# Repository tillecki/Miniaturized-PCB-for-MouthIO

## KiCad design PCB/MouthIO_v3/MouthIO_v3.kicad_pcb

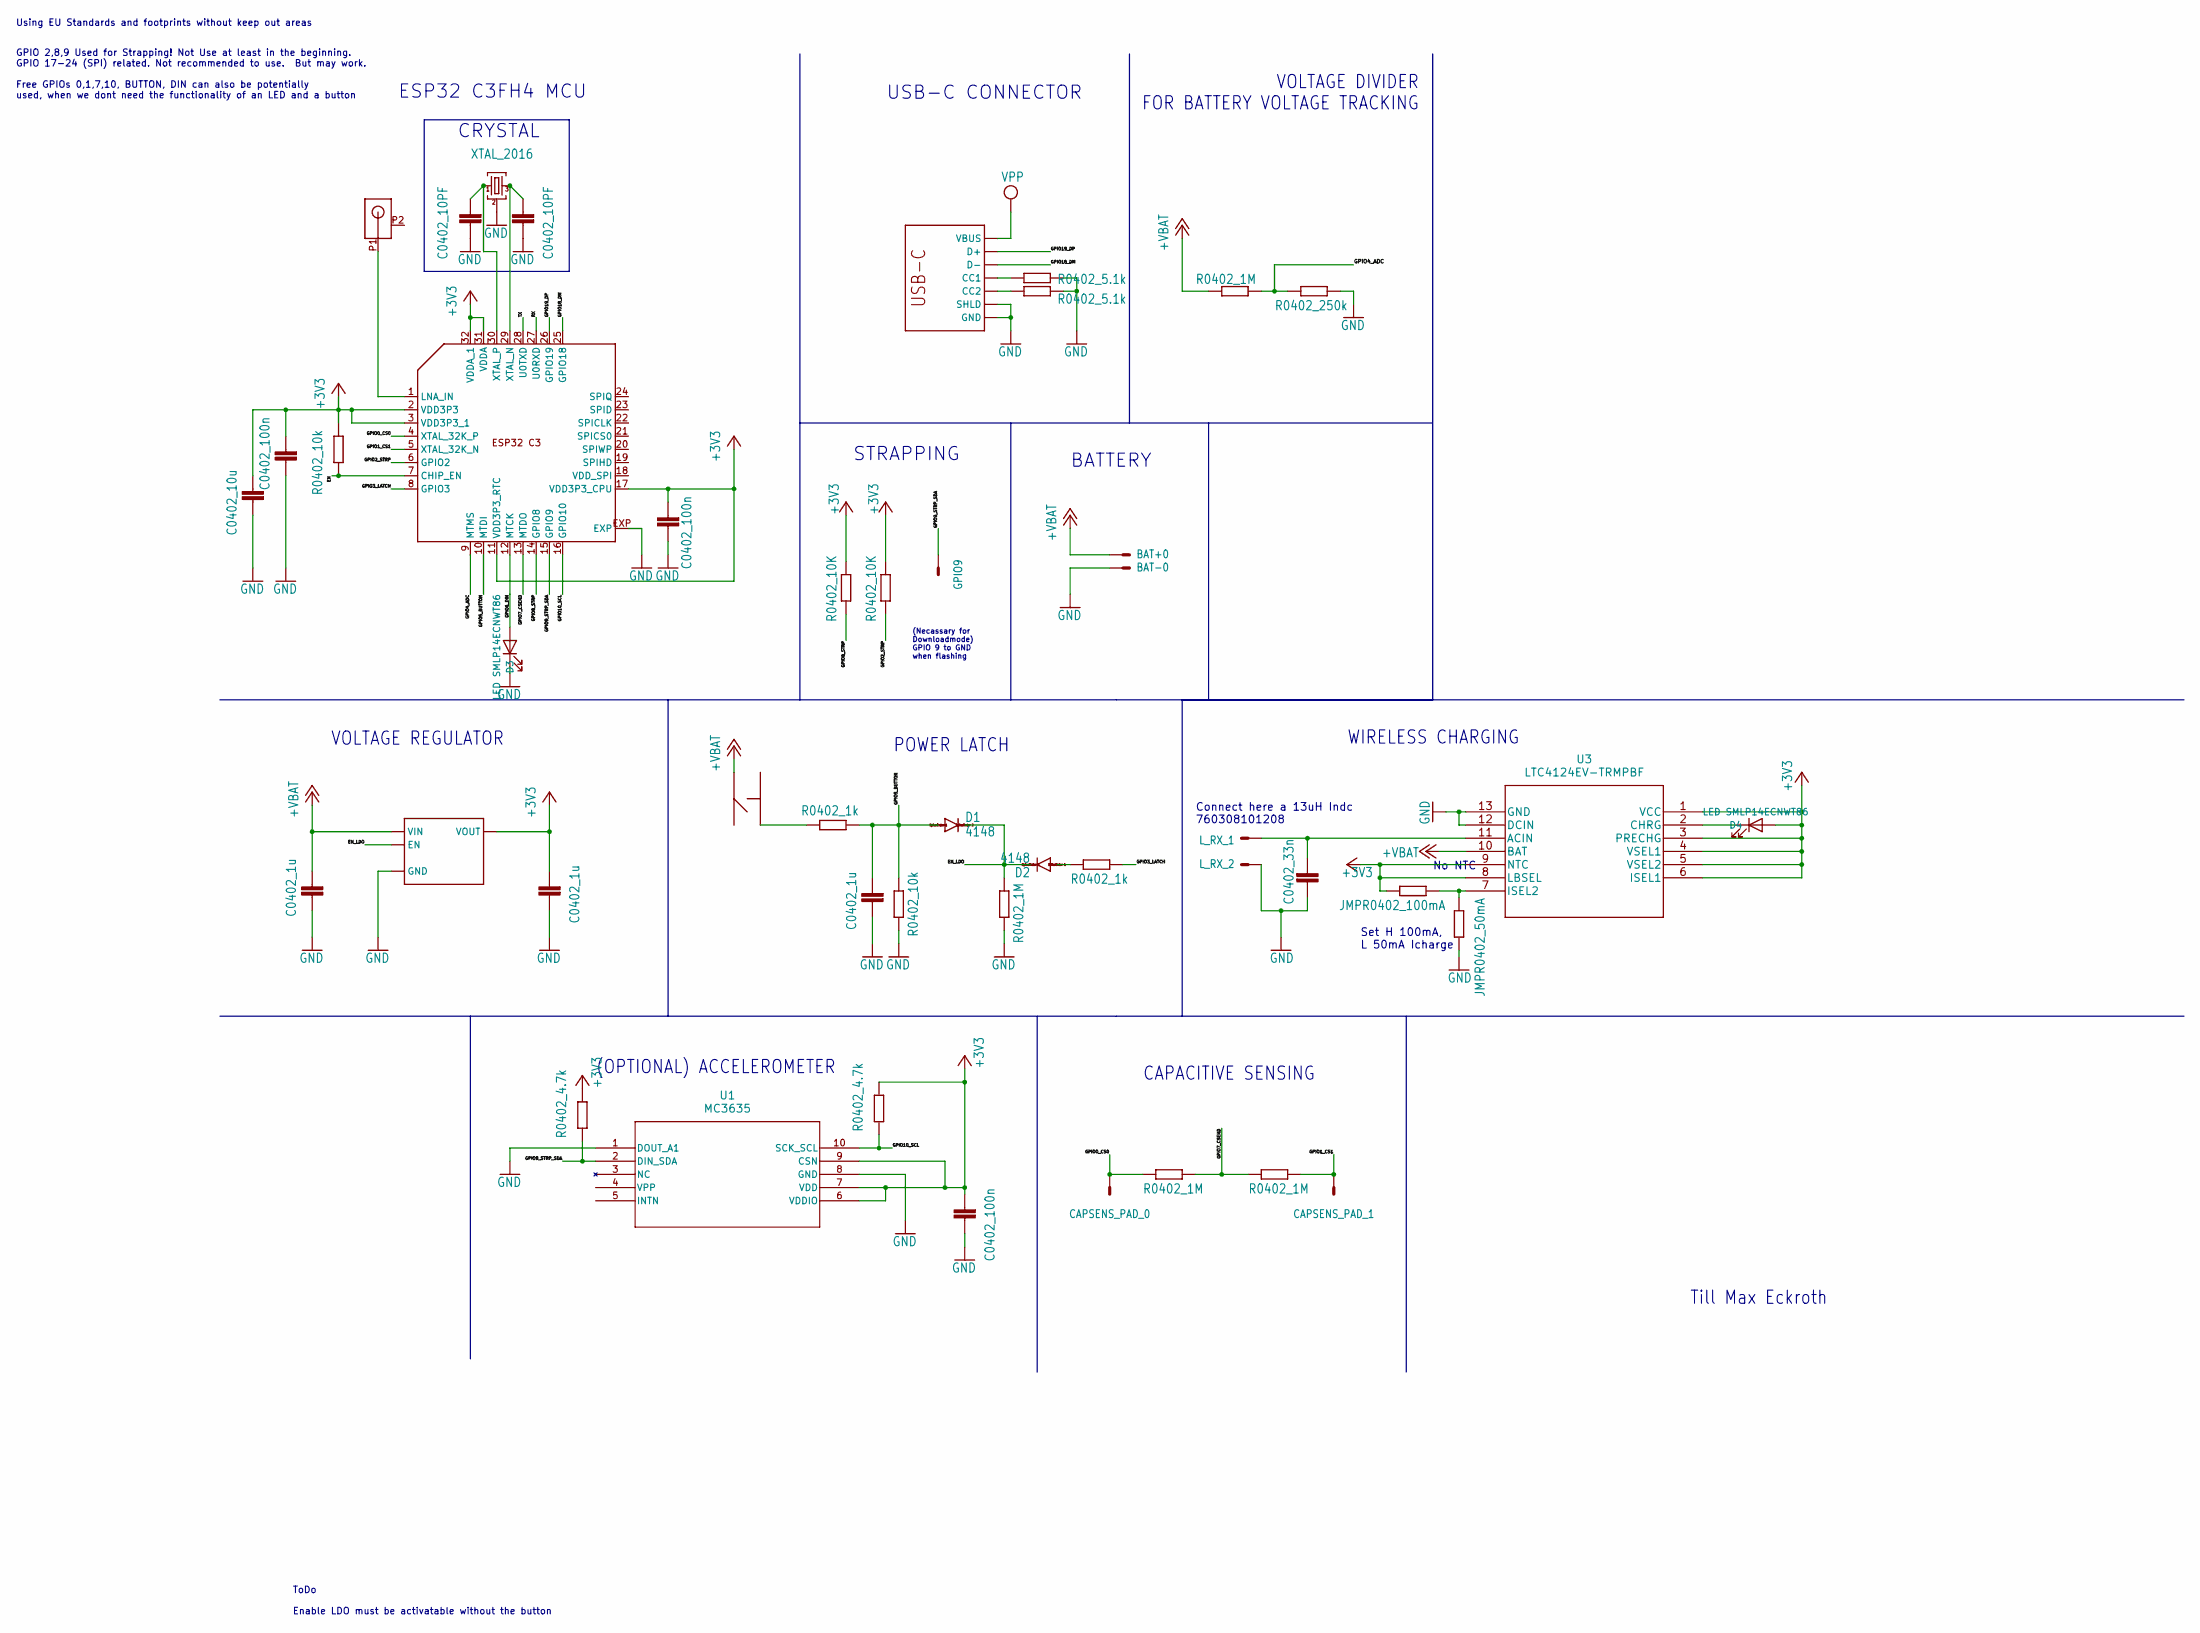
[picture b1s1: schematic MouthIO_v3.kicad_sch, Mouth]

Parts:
BAT+0: TP/SP-1.5X1.0; Solderpad_1.5_1.0
BAT-0: TP/SP-1.5X1.0; Solderpad_1.5_1.0
C1, C2, C13: C0402_1u; C0402_S
C3: C0402_100n; C_0402_1005Metric
C4: C0402_33n; C_0402_1005Metric
C7: C0402_10u; C0402_S
C8, C9: C0402_100n; C0402_S
C20, C21: C0402_10PF; C0402_S
CAPSENS_PAD_0, CAPSENS_PAD_1: TP/SP-1.5X1.0; Solderpad_1.5_1.0
D1, D2: 4148; SOD523
D3, D4: LED SMLP14ECNWT86; R_0402_1005Metric
ESP1: ESP32_C3_QFN32; QFN32
GPIO9: TP/SP-1.5X1.0; Solderpad_1.5_1.0
L_RX_1, L_RX_2: TP/SP-1.5X1.0; Solderpad_1.5_1.0
R1, R2: R0402_1k; R0402
R3: R0402_1M; R0402
R4, R7: R0402_10k; R0402
R5, R6: R0402_4.7k; R_0402_1005Metric
R8, R9: R0402_1M; R_0402_1005Metric
R10, R11: R0402_10K; R0402
R12, R13: R0402_5.1k; R0402
R15: JMPR0402_100mA; R_0402_1005Metric
R16: JMPR0402_50mA; R_0402_1005Metric
R/1: R0402_1M; R0402
R/2: R0402_250k; R0402
RF0: ANT3216LL00R2400A
U1: MC3635; MC3635_MEM-L
U2: MIC5504; TDFN4
U3: LTC4124EV-TRMPBF
U$1: BUTTON_ST-1187-3
USB-C0: USB_C_C393939; USBC_C393939
X1: XTAL_2016; XTYL_2016

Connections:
+3V3: C2.P$2 (2), C3.2, C7.P$2 (2), C8.P$2 (2), C9.P$2 (2), D4.2 (A), ESP1.2 (VDD3P3), ESP1.3 (VDD3P3_1), ESP1.11 (VDD3P3_RTC), ESP1.17 (VDD3P3_CPU), ESP1.31 (VDDA), ESP1.32 (VDDA_1), R5.1, R6.1, R7.1, R10.1, R11.1, R15.2, U1.6 (VDDIO), U1.7 (VDD), U1.9 (CSN), U2.P1 (VOUT), U3.1 (VCC), U3.3 (PRECHG), U3.4 (VSEL1), U3.5 (VSEL2), U3.6 (ISEL1), U3.8 (LBSEL), U3.9 (NTC)
+VBAT: BAT+0.1 (S), C1.P$2 (2), R/1.1, U2.P4 (VIN), U3.10 (BAT), U$1.P2; also elsewhere on the board
/EN: ESP1.7 (CHIP_EN), R7.2
/EN_LDO: D1.C, D2.C, R3.2, U2.P3 (EN)
/GPIO0_CS0: CAPSENS_PAD_0.1 (S), ESP1.4 (XTAL_32K_P), R8.1
/GPIO1_CS1: CAPSENS_PAD_1.1 (S), ESP1.5 (XTAL_32K_N), R9.2
/GPIO2_STRP: ESP1.6 (GPIO2), R11.2
/GPIO3_LATCH: ESP1.8 (GPIO3), R2.2
/GPIO4_ADC: ESP1.9 (MTMS), R/1.2, R/2.1
/GPIO5_BUTTON: C13.P$2 (2), D1.A, ESP1.10 (MTDI), R1.1, R4.2
/GPIO6_DIN: D3.2 (A), ESP1.12 (MTCK)
/GPIO7_CSEND: ESP1.13 (MTDO), R8.2, R9.1
/GPIO8_STRP: ESP1.14 (GPIO8), R10.2
/GPIO9_STRP_SDA: ESP1.15 (GPIO9), GPIO9.1 (S), R5.2, U1.2 (DIN_SDA)
/GPIO10_SCL: ESP1.16 (GPIO10), R6.2, U1.10 (SCK_SCL)
/GPIO18_DM: ESP1.25 (GPIO18), USB-C0.A7 (D-), USB-C0.B7 (D-)
/GPIO19_DP: ESP1.26 (GPIO19), USB-C0.A6 (D+), USB-C0.B6 (D+)
/RX: ESP1.27 (U0RXD)
/TX: ESP1.28 (U0TXD)
GND: BAT-0.1 (S), C1.P$1 (1), C2.P$1 (1), C3.1, C4.1, C7.P$1 (1), C8.P$1 (1), C9.P$1 (1), C13.P$1 (1), C20.P$1 (1), C21.P$1 (1), D3.1 (K), ESP1.EXP, L_RX_2.1 (S), R3.1, R4.1, R12.2, R13.2, R16.2, R/2.2, U1.1 (DOUT_A1), U1.8 (GND), U2.EXP (GND), U2.P2 (GND), U3.12 (DCIN), U3.13 (GND), USB-C0.A1B12 (GND), USB-C0.B1A12 (GND), USB-C0.S1 (SHLD), USB-C0.S2 (SHLD), USB-C0.S3 (SHLD), USB-C0.S4 (SHLD), X1.P2 (G), X1.P4 (G); also elsewhere on the board
unnamed: C20.P$2 (2), ESP1.30 (XTAL_P), X1.P1 (1)
unnamed: C21.P$2 (2), ESP1.29 (XTAL_N), X1.P3 (2)
unnamed: D2.A, R2.1
unnamed: D4.1 (K), U3.2 (CHRG)
unnamed: ESP1.1 (LNA_IN), RF0.P1 (ANT)
unnamed: C4.2, L_RX_1.1 (S), U3.11 (ACIN)
unnamed: R1.2, U$1.P3
unnamed: R15.1, R16.1, U3.7 (ISEL2)
unnamed: R12.1, USB-C0.A5 (CC1)
unnamed: R13.1, USB-C0.B5 (CC2)
VPP: USB-C0.A4B9 (VBUS), USB-C0.B4A9 (VBUS)

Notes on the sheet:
(Necassary for Downloadmode) GPIO 9 to GND when flashing
WIRELESS CHARGING
BATTERY
(OPTIONAL) ACCELEROMETER
CAPACITIVE SENSING
Set H 100mA, L 50mA Icharge
USB-C CONNECTOR
VOLTAGE REGULATOR
No NTC
CRYSTAL
Connect here a 13uH Indc 760308101208
Using EU Standards and footprints without keep out areas
STRAPPING
GPIO 2,8,9 Used for Strapping! Not Use at least in the beginning. GPIO 17-24 (SPI) related. Not recommended to use. But may work. Free GPIOs 0,1,7,10, BUTTON, DIN can also be potentially used, when we dont need the functionality of an LED and a button
ToDo Enable LDO must be activatable without the button
POWER LATCH
VOLTAGE DIVIDER FOR BATTERY VOLTAGE TRACKING
Till Max Eckroth
ESP32 C3FH4 MCU

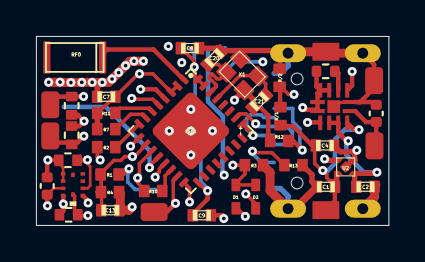
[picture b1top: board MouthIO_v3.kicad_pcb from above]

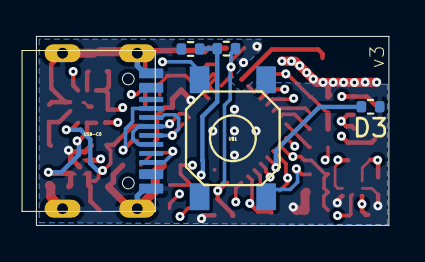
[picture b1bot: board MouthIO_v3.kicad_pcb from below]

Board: 4 copper layers, 19.6 x 10.5 mm, 47 parts (5 on the bottom side), 29 nets.

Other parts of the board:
C4#2: C-EU-0402-WOKEEPOUT_S; C0402_S

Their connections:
+VBAT: C4#2.P$2 (2); also elsewhere on the board
GND: C4#2.P$1 (1); also elsewhere on the board
